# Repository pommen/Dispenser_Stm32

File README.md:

# Dispener_controller
A custom gluedispenser controller for automated gluing. Based on Stm32f103 bluepill

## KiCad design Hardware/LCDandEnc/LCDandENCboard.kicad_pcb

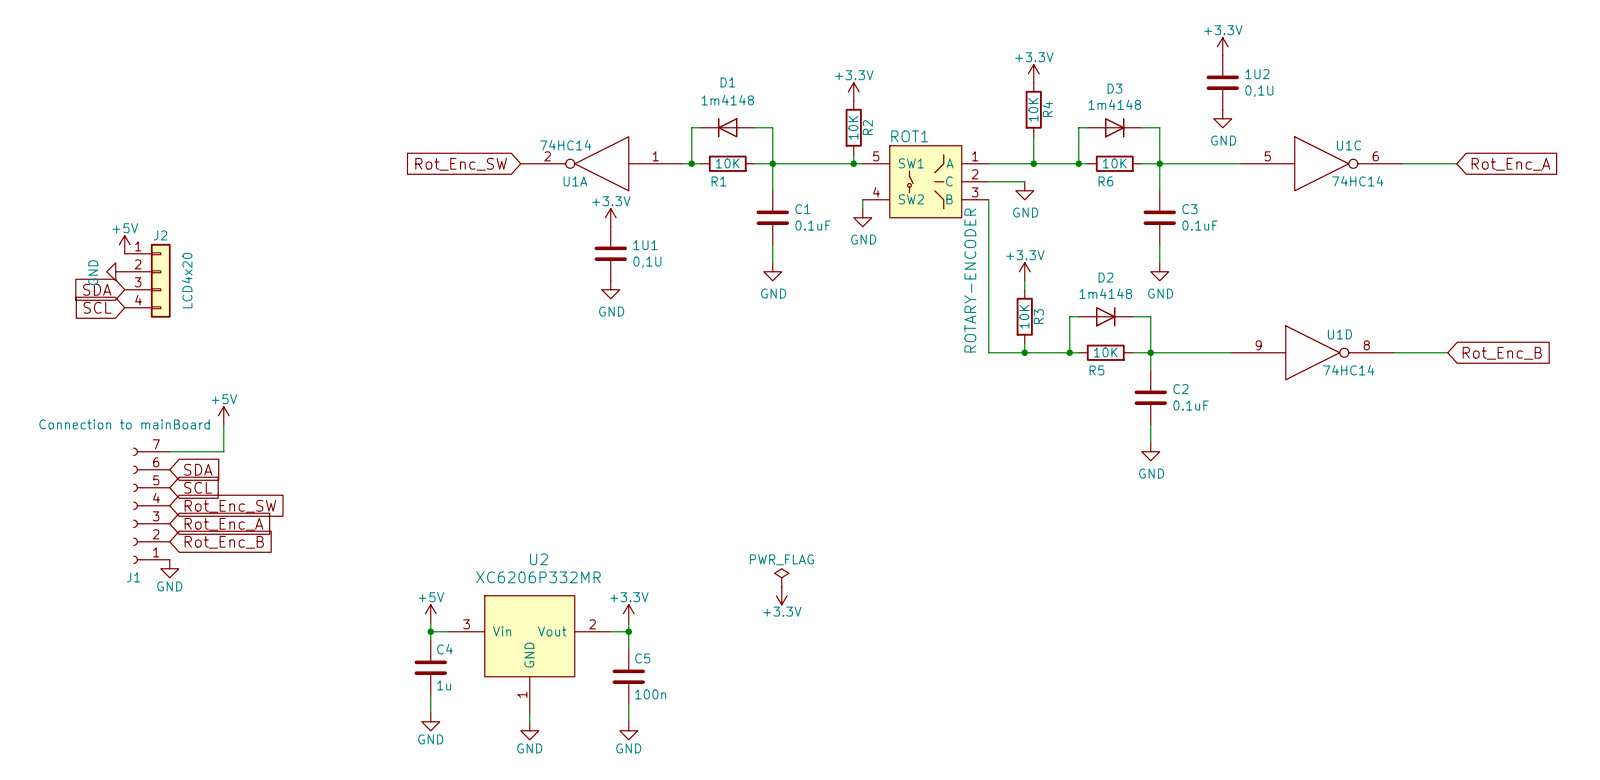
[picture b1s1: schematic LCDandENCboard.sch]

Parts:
1U1, 1U2: 0,1U; C_0805_HandSoldering
C1, C2, C3: 0.1uF; C_0805_HandSoldering
C4: 1u; C_0805_HandSoldering
C5: 100n; C_0805_HandSoldering
D1, D2, D3: 1m4148; D_MiniMELF_Handsoldering
J1: Connection to mainBoard; Pin_Header_Straight_1x07_Pitch2.54mm
J2: LCD4x20; Pin_Header_Straight_1x04_Pitch2.54mm
R1, R2, R3, R4, R5, R6: 10K; R_0805_HandSoldering
ROT1: ROTARY-ENCODER; ROTARY-ENCODER-Ebay
U1: 74HC14; SOIC-14_3.9x8.7mm_Pitch1.27mm
U2: XC6206P332MR; TSOT-23_HandSoldering

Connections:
+3V3: 1U1.1, 1U2.1, C5.1, R2.1, R3.1, R4.1, U2.2 (Vout)
+5V: C4.1, J1.7, J2.1, U2.3 (Vin)
GND: 1U1.2, 1U2.2, C1.2, C2.2, C3.2, C4.2, C5.2, J1.1, J2.2, ROT1.2 (C), ROT1.4 (SW2), U1.7 (GND), U2.1 (GND)
unnamed: C1.1, D1.2 (A), R1.2, R2.2, ROT1.5 (SW1)
unnamed: C2.1, D2.1 (K), R5.2, U1.9
unnamed: C3.1, D3.1 (K), R6.2, U1.5
unnamed: D1.1 (K), R1.1, U1.1
unnamed: D2.2 (A), R3.2, R5.1, ROT1.3 (B)
unnamed: D3.2 (A), R4.2, R6.1, ROT1.1 (A)
Rot_Enc_A: J1.3, U1.6
Rot_Enc_B: J1.2, U1.8
Rot_Enc_SW: J1.4, U1.2
SCL: J1.5, J2.4
SDA: J1.6, J2.3

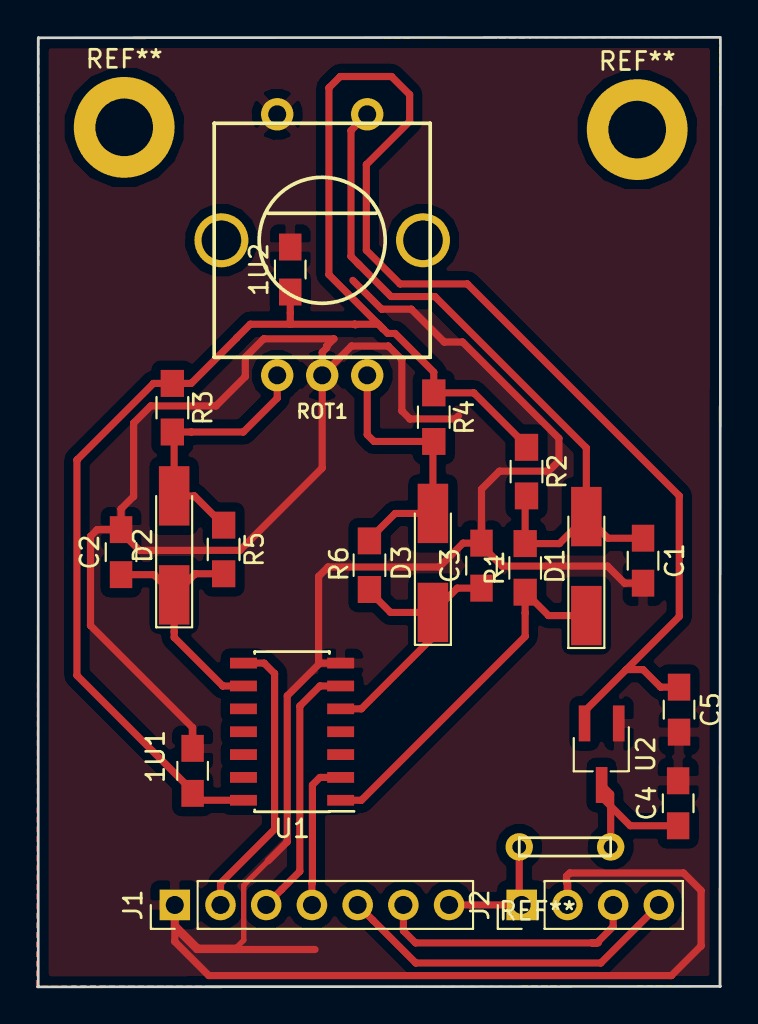
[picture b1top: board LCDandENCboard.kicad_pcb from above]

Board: 2 copper layers, 38.0 x 52.8 mm, 21 parts (0 on the bottom side), 14 nets.

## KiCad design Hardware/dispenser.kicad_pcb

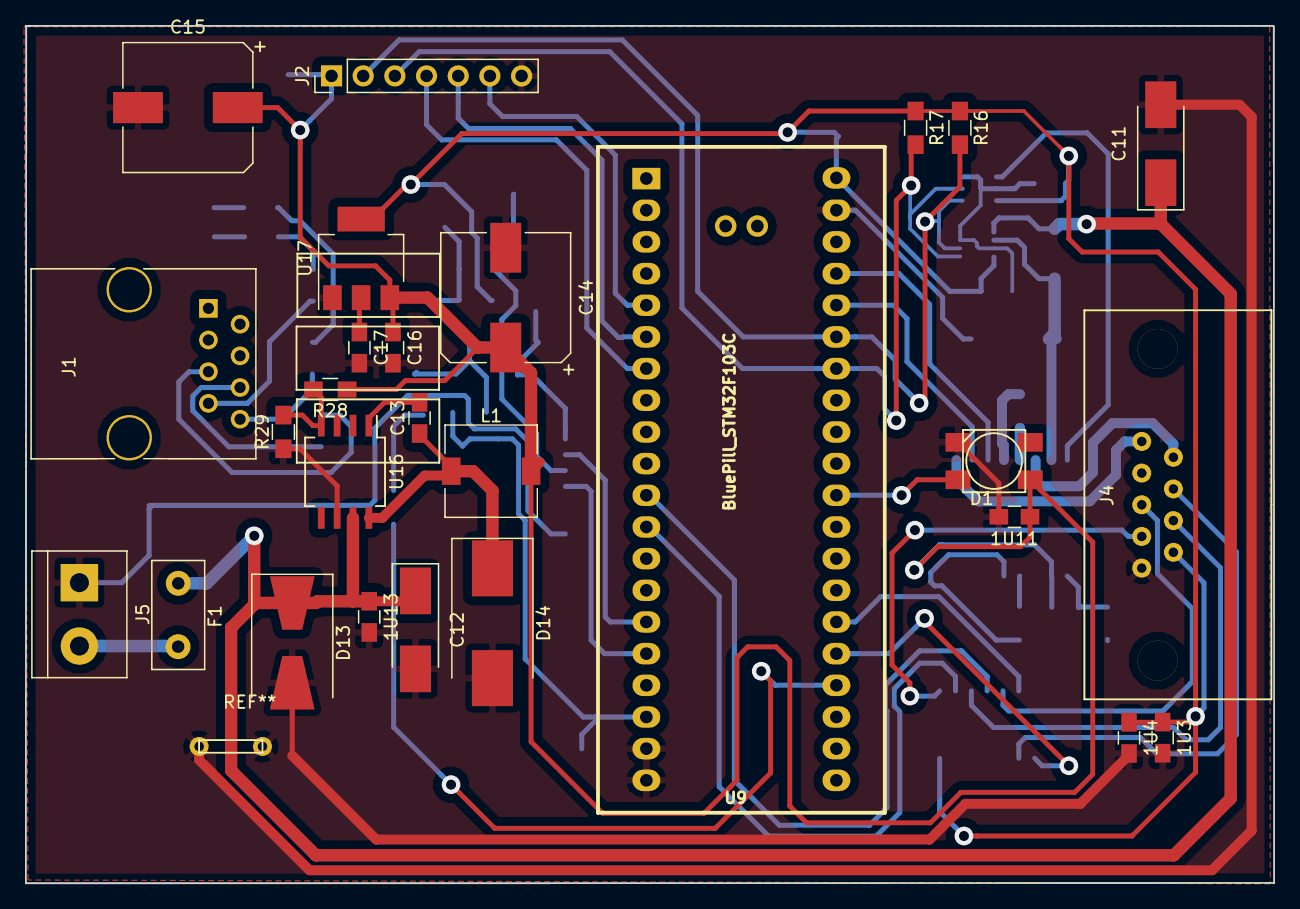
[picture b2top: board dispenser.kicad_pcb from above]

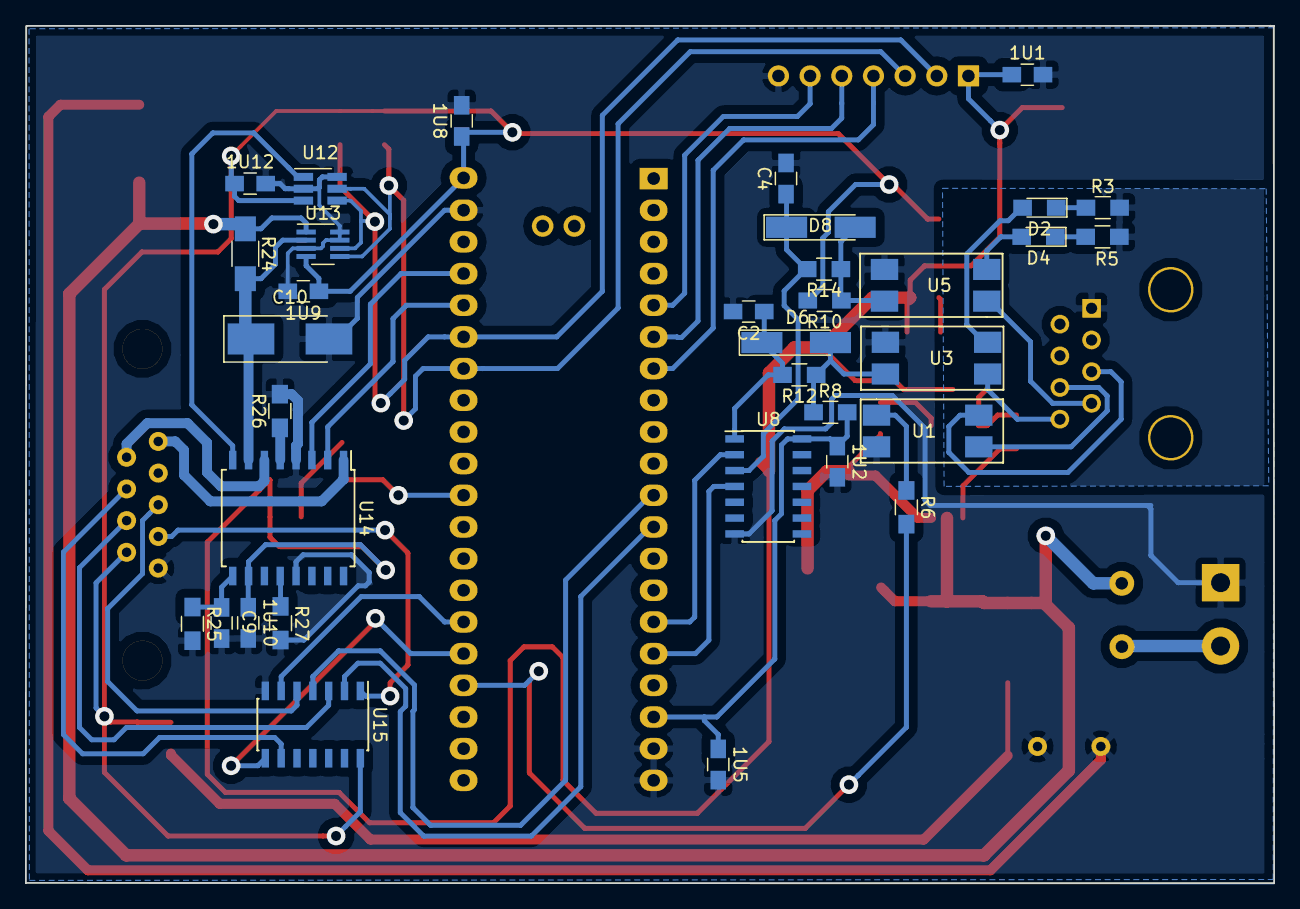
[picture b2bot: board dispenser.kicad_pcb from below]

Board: 2 copper layers, 100.1 x 68.8 mm, 61 parts (34 on the bottom side), 48 nets.

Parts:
1U1, 1U2, 1U3, 1U4, 1U5, 1U8, 1U9, 1U10, 1U11, 1U12: 0,1U; C_0805_HandSoldering
1U13: 0.1uf; C_0805_HandSoldering
C2, C4: 0.1uF; C_0805_HandSoldering
C9: 680pF; C_0805_HandSoldering
C10: 47uF; CP_Tantalum_Case-C_EIA-6032-28_Hand
C11, C12: 4.7uF tant; CP_Tantalum_Case-C_EIA-6032-28_Hand
C13: 10nf; C_0805_HandSoldering
C14: 68Uf; CP_Elec_10x10
C15: 120Uf; CP_Elec_10x10
C16, C17: 1u; C_0805_HandSoldering
D1: WS2812B
D2, D4: LED; LED_0805_HandSoldering
D6: 1m4148; D_MiniMELF_Handsoldering
D8: 1n4148; D_MiniMELF_Handsoldering
D13: D; D_SMB-SMC_Universal_Handsoldering
D14: D_Schottky; D_SMC_Handsoldering
F1: 500mA; Fuse_TE5_Littlefuse-395Series
J1: RJ45; RJ45_8
J2: LCD_and_RotEnc; Pin_Header_Straight_1x07_Pitch2.54mm
J4: Motor1_con; Dsub9
J5: Vin; TerminalBlock_bornier-2_P5.08mm
L1: 47uH; L_7.3x7.3_H4.5
R3, R5, R29: 1K; R_0805_HandSoldering
R6: 120R; R_0805_HandSoldering
R8, R10, R12, R14: 10K; R_0805_HandSoldering
R16, R17: 2K; R_0805_HandSoldering
R24: 0,1R; R_1206_HandSoldering
R25: 56K; R_0805_HandSoldering
R26, R27: 0R5; R_0805_HandSoldering
R28: 3K; R_0805_HandSoldering
U1, U3, U5: PC817; 817opto
U8, U15: 74HC14; SOIC-14_3.9x8.7mm_Pitch1.27mm
U9: BluePill_STM32F103C
U12: MCP4725; SOT-23-6_Handsoldering
U13: ina219; SOT-23-8_Handsoldering
U14: A3968; SOIC-16W_7.5x10.3mm_Pitch1.27mm
U16: LM2675; SO-8_5.3x6.2mm_Pitch1.27mm
U17: ADP3338AKCZ; SOT-223-3_TabPin2

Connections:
+3V3: 1U2.1, 1U3.1, 1U4.1, 1U5.1, 1U8.1, 1U9.1, 1U12.1, C17.1, J4.6, R8.2, R10.2, R16.1, R17.1, U8.14, U9.18, U9.40, U12.3, U13.4, U15.14, U17.2
+24Logic: J1.5, U1.4
+24V: 1U13.1, C11.1, C12.1, D13.1, F1.1, R24.1, U13.1, U16.7
/MotorDriver/M1A: J4.5, U14.1
/MotorDriver/M1B: J4.9, U14.6
CMD_M1: U8.2, U9.15
ENC_A_M1: U9.11, U15.4
ENC_B_M1: U9.12, U15.2
GND: 1U1.2, 1U2.2, 1U3.2, 1U4.2, 1U5.2, 1U8.2, 1U9.2, 1U10.2, 1U11.2, 1U12.2, 1U13.2, C2.2, C4.2, C9.2, C10.2, C11.2, C12.2, C14.2, C15.2, C16.2, C17.2, D1.1, D13.2, D14.2, J2.7, J4.1, J5.1, R25.2, R26.2, R27.2, R29.1, U1.2, U3.3, U5.3, U8.7, U9.19, U9.20, U9.39, U12.2, U12.6, U13.3, U13.7, U13.8, U14.4, U14.13, U15.7, U16.6, U17.1
GNDD: J1.1, R3.2, R5.2
LED: D1.2, U9.30
Limit_LOWER_M1: U9.26, U15.6
Limit_UPPER_M1: U9.25, U15.8
Motor_Input_1A: U9.36, U14.2
Motor_Input_1B: U9.37, U14.3
unnamed: C2.1, D6.1, R12.2, U8.1
unnamed: C4.1, D8.1, R14.2, U8.3
unnamed: C9.1, R25.1, U14.9
unnamed: C10.1, R24.2, U13.2, U14.7
unnamed: C13.1, D14.1, L1.1, U16.8
unnamed: C13.2, U16.1
unnamed: D2.1, R3.1
unnamed: D2.2, U3.2
unnamed: D4.1, R5.1
unnamed: D4.2, U5.2
unnamed: D6.2, R8.1, R12.1, U3.4
unnamed: D8.2, R10.1, R14.1, U5.4
unnamed: F1.2, J5.2
unnamed: J1.6, U1.3
unnamed: J1.7, U5.1
unnamed: J1.8, U3.1
unnamed: J4.2, U15.1
unnamed: J4.3, U15.5
unnamed: J4.7, U15.3
unnamed: J4.8, U15.9
unnamed: R6.1, U1.1
unnamed: R26.1, U14.5
unnamed: R27.1, U14.12
unnamed: R28.2, R29.2, U16.4
unnamed: U12.1, U14.8
OUT_M1: R6.2, U9.24
Rot_Enc_A: J2.5, U9.6
Rot_Enc_B: J2.6, U9.5
Rot_Enc_SW: J2.4, U9.7
SCL: J2.3, R17.2, U9.34, U12.5, U13.5
SDA: J2.2, R16.2, U9.35, U12.4, U13.6
Step_M1: U8.4, U9.16
VDD: 1U1.1, 1U10.1, 1U11.1, C14.1, C15.1, C16.1, D1.3, J2.1, L1.2, R28.1, U14.10, U17.3

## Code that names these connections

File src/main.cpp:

/*
   I2C addresses:

   LCD:0x3F (63)
   DAC:0x60 (96)
   INA: 0x40 (64)

   todo's:

   meny system:{
   step back efter körning
   Current limit
   Hastighet (PWM)
   simulate command
   }

   LED?
   Motor divare fram och bak (Servo?) - Funkar. behöver bättre funktion
   command input (anväanda samma som den gamla?)



   MAX 1.3V dac.
   3.3/4096 = 0.000805664 vOLT/step
   1,3v = 1613 STEPS
   Divide by 3 i hardware?

   Itrip= Vref /(4rs) = vref / 2


 */
 #include <Arduino.h>
 #include <Wire.h>
 #include <LiquidCrystal_I2C.h>
 #include <Adafruit_MCP4725.h>
 #include <Adafruit_INA219.h>
 #include <Adafruit_NeoPixel-ANDnXOR.h>
 #include <PID_v1.h>
 #include <Bounce2.h>
#include <EEPROM.h>



//Pins: Must be in the same .h file as they are used.

int motor1_input1 = PB8;
int motor1_input2 = PB9;

int step_M1 = PB11;
int cmd_M1 = PB10;

const int limitUpper_M1 = PB0;
const int limitLower_M1= PB1;
const int out_M1 = PB15;
const int LED = PA13;

int motor1_Enc_A = PA6;
int motor1_Enc_B = PA7;
int rot_EncA = PA0;
int rot_EncB = PA1;
int rot_EncBTN = PA2;

//Define Variables we'll be connecting to
double Setpoint, Input, Output;

//Specify the links and initial tuning parameters
<<<<<<< HEAD
double Kp=99.99, Ki=99.99, Kd=99.99;
=======
double Kp=99, Ki=99, Kd=99;
>>>>>>> bd115d1200da04cd67c7518dda64e173ee50fe06
PID myPID(&Input, &Output, &Setpoint, Kp, Ki, Kd,P_ON_M, DIRECT);
//DIRECT
Bounce debouncer = Bounce();
Adafruit_MCP4725 dac;
Adafruit_INA219 ina219;
LiquidCrystal_I2C lcd(0x3f,20,4);


// Parameter 1 = number of pixels in strip
// Parameter 2 = pin number (most are valid)
// Parameter 3 = pixel type flags, add together as needed:
//   NEO_KHZ800  800 KHz bitstream (most NeoPixel products w/WS2812 LEDs)
//   NEO_KHZ400  400 KHz (classic 'v1' (not v2) FLORA pixels, WS2811 drivers)
//   NEO_GRB     Pixels are wired for GRB bitstream (most NeoPixel products)
//   NEO_RGB     Pixels are wired for RGB bitstream (v1 FLORA pixels, not v2)
Adafruit_NeoPixel pixels = Adafruit_NeoPixel(1, LED, NEO_GRB + NEO_KHZ800);



//Eeprom addresses 10 byte per adress, just to be safe (in case of double):
const int Kp_promAddress = 0;
const int Ki_promAddress = 8;
const int Kd_promAddress = 17;
const int MotorCurrent_promAddress = 25;
const int MotorSpeed_promAddress =34;


//Golbals:

int LCDUpdateTimer =0;
int runonce =12;
int motorSpeed =99;
int motorCurrent=99;
int inaV[5];
int inaA[5];
int inaPointer=0;
int menuTimer =0;
int rot_EncBTN_Bounced = 0;
int location =0;

//Prototypes:

void Motor1_enc_ISR();
void GotCommand();
void Rot_enc_ISR();
void run(int steps);
void Display();
int gotCommand_M1(int pin);
int gotCommand_M2();
void count_pulses();
void i2cScanner();



//my owm files needs to be included last ????!?? <- after pin declaration
#include <enc.h>
#include <menu.h>
#include <gotCommand.h>
#include <runMotor.h>
#include <showSettings.h>
<<<<<<< HEAD
#include <I2C_scanner.h>
=======
>>>>>>> bd115d1200da04cd67c7518dda64e173ee50fe06
void setup(){
        Serial.begin(115200);
        Serial.print("Hello");
        pinMode(motor1_Enc_A, INPUT);
        pinMode(motor1_Enc_B, INPUT);
        pinMode(rot_EncA, INPUT);
        pinMode(rot_EncB, INPUT);
        pinMode(rot_EncBTN, INPUT);

        pinMode(motor1_input1, PWM);
        pinMode(motor1_input2, PWM);
        pwmWrite(motor1_input1, 0);
        pwmWrite(motor1_input2, 0);

        pinMode(cmd_M1, INPUT_PULLUP);
        pinMode(step_M1, INPUT_PULLUP);
        pinMode(limitUpper_M1, INPUT_PULLUP);
        pinMode(limitLower_M1, INPUT_PULLUP);

        pinMode(out_M1, OUTPUT);
        pinMode(LED, OUTPUT);

        lcd.init();            // initialize the lcd
        lcd.backlight();
        lcd.clear();

        // Initialize the INA219.
        // By default the initialization will use the largest range (32V, 2A).  However
        // you can call a setCalibration function to change this range (see comments).
        ina219.begin();
        // To use a slightly lower 32V, 1A range (higher precision on amps):
        ina219.setCalibration_32V_1A(); //32 Volt max 10 A
        // Or to use a lower 16V, 400mA range (higher precision on volts and amps):
        //ina219.setCalibration_16V_400mA();

        dac.begin(0x60);

        myPID.SetMode(AUTOMATIC);


        attachInterrupt(motor1_Enc_A, Motor1_enc_ISR, FALLING);
        attachInterrupt(rot_EncA, Rot_enc_ISR, FALLING);

        debouncer.attach(rot_EncBTN);
        debouncer.interval(5);




        LCDUpdateTimer =millis();
        digitalWrite(out_M1, LOW);

        delay(50); //låter DAC'en stabilisera

//Läser tuning variabler från Eeprom och skriver dom
<<<<<<< HEAD
        Kp = EEPROM.read(Kp_promAddress) /10;
        Ki = EEPROM.read(Ki_promAddress) /10;
        Kd = EEPROM.read(Kd_promAddress) /10;
=======
        Kp = EEPROM.read(Kp_promAddress);
        Ki = EEPROM.read(Ki_promAddress);
        Kd = EEPROM.read(Kd_promAddress);
>>>>>>> bd115d1200da04cd67c7518dda64e173ee50fe06
        myPID.SetTunings(Kp, Ki, Kd);
        motorCurrent = EEPROM.read(MotorCurrent_promAddress);
        motorSpeed = EEPROM.read(MotorSpeed_promAddress);
        dac.setVoltage(motorCurrent, false);
        myPID.SetOutputLimits(40000, motorSpeed);

        //showSetting();

}

void loop(){
        debouncer.update();
        rot_EncBTN_Bounced = debouncer.read();

        if (millis() - LCDUpdateTimer >=100) {
                Display();
                LCDUpdateTimer=millis();
        }


        if (digitalRead(cmd_M1) == HIGH) {
                pulses = gotCommand_M1(cmd_M1);

                run(pulses);
        }

        if (digitalRead(limitLower_M1) == LOW) {
                lcd.clear();
                lcd.setCursor(0, 0);
                lcd.print("limit Lower M1");
        }
        if (digitalRead(limitUpper_M1) == LOW) {
                lcd.clear();
                lcd.setCursor(0, 0);
                lcd.print("limit Upper M1");
        }

        if (rot_EncBTN_Bounced == HIGH) {
                lcd.setCursor(0, 0);
                lcd.print(millis() - menuTimer);
                if (millis() - menuTimer > 1000 ) {
                        MainMenu();
                        menuTimer = millis();

                }
        }

        else {
                menuTimer = millis();
        }
}







void Display(/* arguments */) {
        lcd.setCursor(0,0);
        lcd.print("BusV    Bus Current");
        lcd.setCursor(0, 1);
        lcd.print(ina219.getBusVoltage_V());
        lcd.setCursor(13, 1);
        lcd.print(ina219.getCurrent_mA()/10);


        lcd.setCursor(0,2);
        lcd.print(enc_Motor1);
<<<<<<< HEAD
=======
}



void i2cScanner(){
        lcd.clear();
        lcd.print("I2c addresses");
        lcd.setCursor(0,1);
        byte error, address;
        int nDevices;


        nDevices = 0;
        for(address = 1; address < 127; address++ )
        {
                // The i2c_scanner uses the return value of
                // the Write.endTransmisstion to see if
                // a device did acknowledge to the address.
                Wire.beginTransmission(address);
                error = Wire.endTransmission();

                if (error == 0)
                {
                        lcd.print("0x");
                        if (address<16)
                                lcd.print("0");
                        lcd.print(address,HEX);
                        lcd.print(" ");

                        nDevices++;
                }
                else if (error==4)
                {
                        lcd.print("Unknown 0x");
                        if (address<16)
                                lcd.print("0");
                        lcd.println(address,HEX);
                }
        }
        if (nDevices == 0)
                lcd.println("No I2C devices found\n");
        else
                lcd.setCursor(0,3);

        lcd.print("Done Sanning");
        delay(1000);
        while (1) {
                if (digitalRead(rot_EncBTN) == HIGH) {
                        break;
                        /* code */
                }
        }

>>>>>>> bd115d1200da04cd67c7518dda64e173ee50fe06
}

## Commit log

2018-01-29 First commit
    First commit. Schemtic needs confirming. Layout begun.
    Check PWM timers and Interupts
2018-01-29 Updated for platformio
2018-01-31 Börjar ta form
2018-01-31 more splitting
2018-01-31 External commands added
2018-02-01 Both motors and dac scaling
2018-02-07 Inputs working
2018-02-08 Add files via upload
    HW layout and libs
2018-02-12 Layout - some pin changes to 74hc14
2018-03-19 one motor
2018-03-19 Flatcam and grbl
2018-03-25 layout and BOM
2018-03-25 Bad I2C pinout
    Swappe some pins around to match the i2c lcd board
2018-04-02 Getting there
